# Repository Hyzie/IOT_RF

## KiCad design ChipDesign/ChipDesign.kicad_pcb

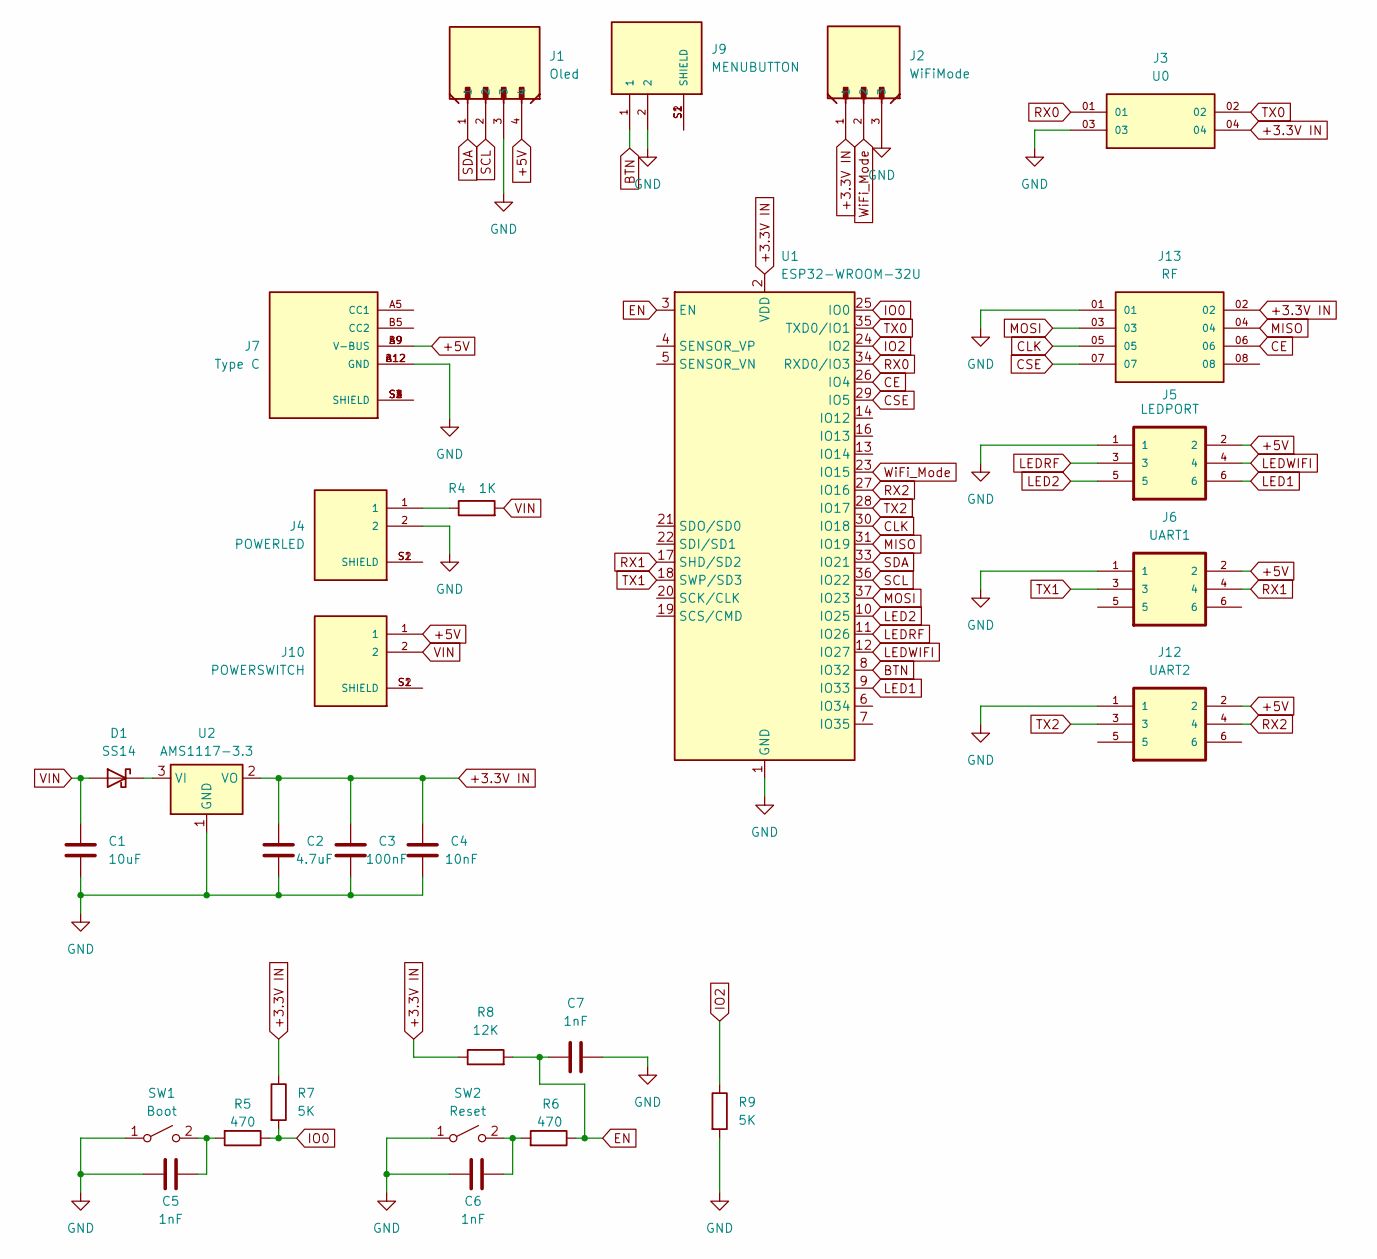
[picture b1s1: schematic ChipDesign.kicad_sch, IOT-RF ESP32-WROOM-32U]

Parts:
C1: 10uF; C_0805_2012Metric_Pad1.18x1.45mm_HandSolder
C2: 4.7uF; C_0805_2012Metric_Pad1.18x1.45mm_HandSolder
C3: 100nF; C_0805_2012Metric_Pad1.18x1.45mm_HandSolder
C4: 10nF; C_0805_2012Metric_Pad1.18x1.45mm_HandSolder
C5, C6, C7: 1nF; C_0805_2012Metric_Pad1.18x1.45mm_HandSolder
D1: SS14; D_SMA
J1: Oled; HRS_DF13A-4P-1.25H_21_
J2: WiFiMode; HRS_DF13A-3P-1.25H_21_
J3: U0; SAMTEC_RSM-102-02-S-D; PARTREV D
J4: POWERLED; HRS_DF13A-2P-1.25H_51_; PARTREV March 2020
J5: LEDPORT; TE_2-1761603-1; PARTREV B1
J6: UART1; TE_2-1761603-1; PARTREV B1
J7: Type C; CUI_UJC-HP-3-SMT-TR; PARTREV 04/30/2020
J9: MENUBUTTON; HRS_DF13A-2P-1.25H_51_; PARTREV March 2020
J10: POWERSWITCH; HRS_DF13A-2P-1.25H_51_; PARTREV March 2020
J12: UART2; TE_2-1761603-1; PARTREV B1
J13: RF; SAMTEC_TSS-104-01-G-D; PARTREV R
R4: 1K; R_0805_2012Metric_Pad1.20x1.40mm_HandSolder
R5, R6: 470; R_0805_2012Metric_Pad1.20x1.40mm_HandSolder
R7: 5K; R_0805_2012Metric_Pad1.20x1.40mm_HandSolder
R8: 12K; R_0805_2012Metric_Pad1.20x1.40mm_HandSolder
R9: 5K; R_0805_2012Metric
SW1: Boot; SW_Push_SPST_NO_Alps_SKRK
SW2: Reset; SW_Push_SPST_NO_Alps_SKRK
U1: ESP32-WROOM-32U
U2: AMS1117-3.3; SOT-223-3_TabPin2

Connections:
+3.3V IN: C2.1, C3.1, C4.1, J2.1, J3.04, J13.02, R7.1, R8.1, U1.2 (VDD), U2.2 (VO)
+5V: J1.4, J5.2, J6.2, J7.A9 (V-BUS), J7.B9 (V-BUS), J10.1, J12.2
BTN: J9.1, U1.8 (IO32)
CE: J13.06, U1.26 (IO4)
CLK: J13.05, U1.30 (IO18)
CSE: J13.07, U1.29 (IO5)
EN: C7.1, R6.1, R8.2, U1.3 (EN)
GND: C1.2, C2.2, C3.2, C4.2, C5.2, C6.2, C7.2, J1.3, J2.3, J3.03, J4.2, J5.1, J6.1, J7.A12 (GND), J7.B12 (GND), J9.2, J12.1, J13.01, R9.2, SW1.1 (A), SW2.1 (A), U1.1 (GND), U1.15 (GND), U1.38 (GND), U1.39 (GND), U2.1 (GND)
IO0: R5.1, R7.2, U1.25 (IO0)
IO2: R9.1, U1.24 (IO2)
LED1: J5.6, U1.9 (IO33)
LED2: J5.5, U1.10 (IO25)
LEDRF: J5.3, U1.11 (IO26)
LEDWIFI: J5.4, U1.12 (IO27)
MISO: J13.04, U1.31 (IO19)
MOSI: J13.03, U1.37 (IO23)
unnamed: D1.1 (K), U2.3 (VI)
unnamed: J4.1, R4.1
unnamed: J4.S1 (SHIELD), J4.S2 (SHIELD)
unnamed: J7.S1 (SHIELD), J7.S2 (SHIELD), J7.S3 (SHIELD), J7.S4 (SHIELD)
unnamed: J9.S1 (SHIELD), J9.S2 (SHIELD)
unnamed: J10.S1 (SHIELD), J10.S2 (SHIELD)
unnamed: C5.1, R5.2, SW1.2 (B)
unnamed: C6.1, R6.2, SW2.2 (B)
RX0: J3.01, U1.34 (RXD0/IO3)
RX1: J6.4, U1.17 (SHD/SD2)
RX2: J12.4, U1.27 (IO16)
SCL: J1.2, U1.36 (IO22)
SDA: J1.1, U1.33 (IO21)
TX0: J3.02, U1.35 (TXD0/IO1)
TX1: J6.3, U1.18 (SWP/SD3)
TX2: J12.3, U1.28 (IO17)
VIN: C1.1, D1.2 (A), J10.2, R4.2
WiFi_Mode: J2.2, U1.23 (IO15)

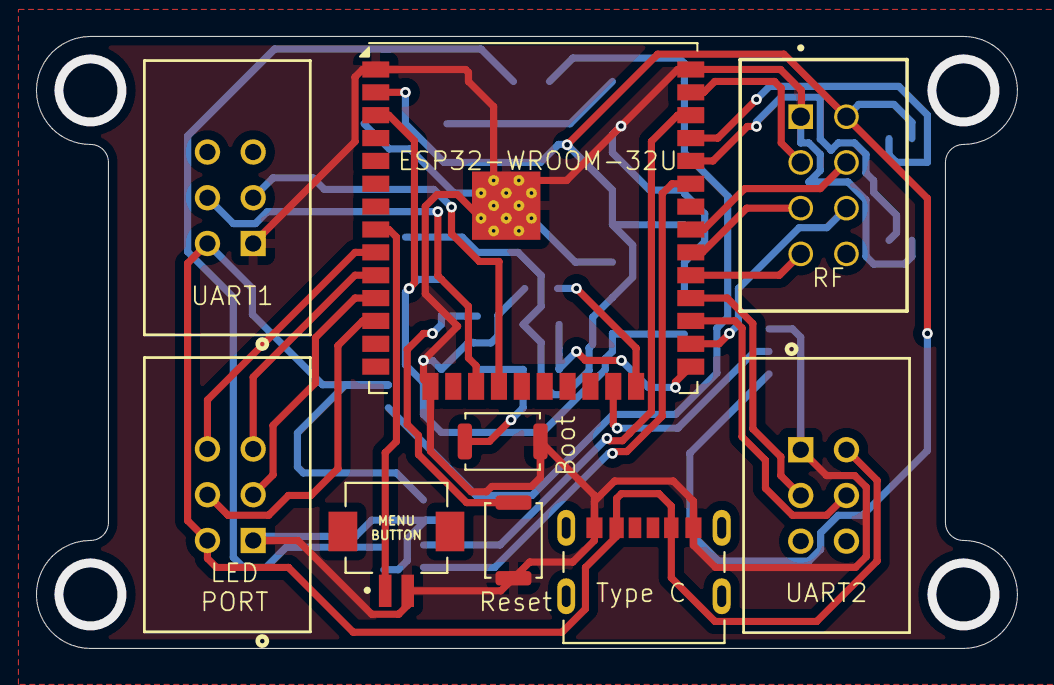
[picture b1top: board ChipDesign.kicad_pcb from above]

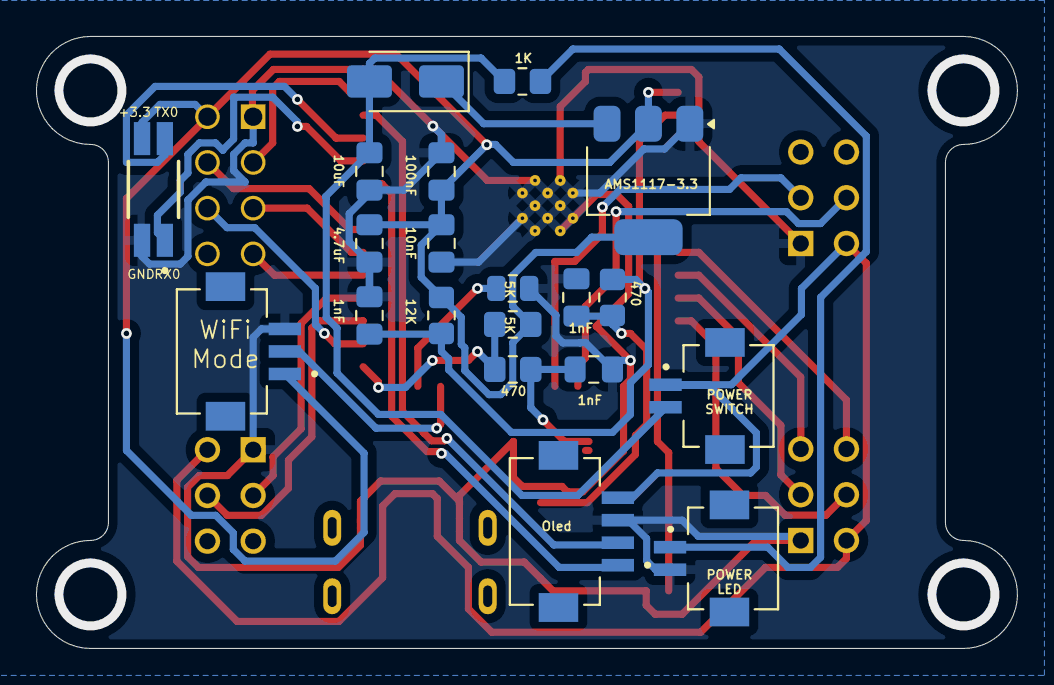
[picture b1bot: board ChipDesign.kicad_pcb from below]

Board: 2 copper layers, 54.5 x 34.0 mm, 29 parts (20 on the bottom side), 34 nets.

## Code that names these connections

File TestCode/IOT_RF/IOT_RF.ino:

#include "system_config.h"

unsigned long lastDebounce = 0;

void IRAM_ATTR handleButtonPress()
{
  unsigned long cur = millis();

  if (cur - lastDebounce > 100) {
    if (state > 3) {
      state = 0;
    }
    else
      state++;

    lastDebounce = cur;
  }
}

void setup() {
  Serial.begin(115200);
  Serial1.begin(9600, SERIAL_8N1, 16, 17);
  Serial2.begin(9600, SERIAL_8N1, RX1, TX1);

  pinMode(LEDWIFI, OUTPUT);
  pinMode(LEDRF, OUTPUT);
  pinMode(LED1, OUTPUT);
  pinMode(LED2, OUTPUT);

  pinMode(WiFi_Mode, INPUT_PULLUP);
  pinMode(BTN, INPUT_PULLUP);

  attachInterrupt(digitalPinToInterrupt(BTN), handleButtonPress, FALLING);

  Wire.begin(SDA_PIN, SCL_PIN);

  if(!display.begin(SSD1306_SWITCHCAPVCC, SCREEN_ADDRESS)) {
    Serial.println(F("SSD1306 allocation failed"));
    for(;;);
  }
  display.display();
  delay(1000); 

  display.clearDisplay();
  display.setTextSize(1);
  display.setTextColor(SSD1306_WHITE);
  display.setCursor(0,0);
  display.println(F("Setting up..."));
  display.display();
  delay(1000);

  ConnectToDB();

  ShowRF();

}

void loop() {
  if(millis() - send_data_timer > 1000 || send_data_timer == 0)
  {
    send_data_timer = millis();

    if(conn.connected())
    {
      // Chỉnh sửa các giá trị để kiểm tra 
      SendData(1, 2, 3, 4, 5, 6);
    }
    else
    {
      conn.close();
      if(conn.connect(server_addr, 3306, user, password, db)) 
      {
        Serial.printf("Reconnected to database: %s", db);
      }
    }
  }

  if(millis() - show_data_timer > 200 || show_data_timer == 0)
  {
    show_data_timer = millis();

    switch(state)
    {
      case 0:
      {
        ShowWiFiInfo(ssid);
        break;
      }
      
      case 1:
      {
        ShowRF();
        break;
      }
      
      case 2:
      {
        ShowUART1();
        break;
      }

      case 3: 
      {
        ShowUART2();
        break;
      }
    }
  }
}


void devide()
{
  display.drawLine(0, 0, 128, 0, WHITE);
  display.drawLine(0, 0, 0, 63, WHITE);
  display.drawLine(0, 63, 127, 63, WHITE);
  display.drawLine(127, 0, 127, 63, WHITE);
  
  display.drawLine(32, 16, 32, 64, WHITE);
  display.drawLine(0, 16, 128, 16, WHITE);
  display.drawLine(0, 32, 128, 32, WHITE);
  display.drawLine(0, 48, 128, 48, WHITE);
}

void ShowWiFiInfo(char* SSID)
{
  display.clearDisplay();

  display.drawLine(0, 0, 128, 0, WHITE);
  display.drawLine(0, 0, 0, 63, WHITE);
  display.drawLine(0, 63, 127, 63, WHITE);
  display.drawLine(127, 0, 127, 63, WHITE);

  display.setCursor(5, 10);
  display.print(F("WiFi: "));
  display.setCursor(5, 32);
  display.println(F(SSID));

  display.display();
}

void ShowRF(){
  display.clearDisplay();
  devide();

  display.setCursor(10, 5);
  display.print(F("RF Module"));

  display.display();
}

void ShowUART1(){
  display.clearDisplay();
  devide();

  display.setCursor(10, 5);
  display.print(F("UART1"));

  display.display();
}

void ShowUART2(){
  display.clearDisplay();
  devide();

  display.setCursor(10, 5);
  display.print(F("UART2"));

  display.display();
}

void ConnectToDB()
{
  Serial.println("Connecting to WiFi...");
  ssid = stoca(Essid());
  pass = stoca(Epass());
  WiFi.begin(ssid, pass);

  display.clearDisplay();
  display.setCursor(4, 10);
  char dpl[128];
  sprintf(dpl, "Connecting to %s ...", ssid); 
  display.println(dpl);
  display.display();

  int count = 20;
  while (WiFi.status() != WL_CONNECTED) {
    delay(500);
    Serial.print(".");
    count--;
    if(count == 0)
    {
      BLEsetup();
      while(1)
      {
        BLErepeat();

        display.clearDisplay();
        display.setCursor(20, 10); 
        display.println("Bluetooth");
        display.setCursor(40, 30);
        display.println("is on.");
        display.display();

        if(WiFi.status() == WL_CONNECTED)
          break;
      }
    }
  }
 
  display.clearDisplay();
  display.setCursor(4, 20);
  display.println("Connected.");
  display.display();
  delay(500);

  Serial.println("\nConnected to WiFi.");
  Serial.print("IP Address: ");
  Serial.println(WiFi.localIP());
  Serial.println("Attempting to connect to MySQL...");

  if(conn.connect(server_addr, 3306, user, password, db)) 
  {
    display.clearDisplay();
    display.setCursor(10, 30);
    display.println("Ready!!!");
    display.display();
    delay(500);
  } 
  else
  {
    while(1)
    {
      if(conn.connect(server_addr, 3306, user, password, db)) 
      {
        delay(500);
        Serial.printf("Reconnected to database: %s", db);
        break;
      }
    }
  }
}

// Convert String into char array
char* stoca(const String& str) {
  char* charArray = new char[str.length() + 1];
  str.toCharArray(charArray, str.length() + 1);
  return charArray;
}

void SendData(float temp, float humid, int a1, int a2, int d1, int d2)
{
  char PROGMEM query[256];
  sprintf(query, "UPDATE iot_monitor SET temperature = %.2f, humidity = %.2f, analog_1 = %d, analog_2 = %d, digital_1 = %d, digital_2 = %d WHERE iot_id = '%s'", temp, humid, a1, a2, d1, d2, device_id);


  MySQL_Cursor *cur_mem = new MySQL_Cursor(&conn);
  cur_mem->execute(query);
  delete cur_mem;
}

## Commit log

2024-09-18 First update
